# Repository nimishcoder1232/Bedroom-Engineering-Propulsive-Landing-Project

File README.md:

# Bedroom-Engineering-Propulsive-Landing-Project
This repo has everything that I made for my rocket that can propulsive landing, while still being under ITAR restrictions. 

For this project, I will design a rocket that can launch and then do a propulsive landing. In order to meet this challenge, I will have to make a new custom ESP32-based flight computer. I will have to make a quaternion orientation calculation system, I will have to design a control loop, and I will have to make a simulator in Python, without vibe coding, because it is too complicated. The simulator will simulate the rocket’s flight to help tune the control loop and the propulsive landing.

I did this project for a few reasons. The first reason I did it, is because in gneral, this is my passion. I love both engineering and rockets, so this is satisfactory for me. This isant a project for me, this project is more, who I am. I also made this project to learn from it. Throughout this project, I have learned sooo much, PCB design, CAD, Programign in many languages, soldering. And SO much more. Every time I sit down to do one of these projects, I end up learning so much. That is the second reason I work on these projects, To learn From them. 

Notes:
I am 3d printing everything myself, I DONT need reinbursment

The cad has all the parts. The engine, and the dc motor, and the syringes, are provided by me. 

The cad is ONE zip file. Once you unpack it, it has ALL the parts. the file in ALL CAPS called FULL ASEMBLY is the completed asembbly. 

No explosives are in any of the BOM, no engines, nothing. 

Project Link: https://blueprint.hackclub.com/projects/7459

Full Rocket: 

PCB schematic: 

PCB Routing: 

PCB Preview: 

Wiring Diagram: 

Any bold line is a electrical wire. I have color coded it. black for ground, red for power, and blue for saignals. if two same color lines touch, thats a connection, if two ddifferent colored lines overlaped, thats NOT a connection. 

|Item Name                                                              |Link                                                                                                                                                                                                                                                              |Quanity|Cost  USD|Notes                                                                             |
|-----------------------------------------------------------------------|------------------------------------------------------------------------------------------------------------------------------------------------------------------------------------------------------------------------------------------------------------------|-------|---------|----------------------------------------------------------------------------------|
|Carbon Fiber Rod 500mm 5 pack                                          |https://www.aliexpress.com/item/3256806607506929.html?spm=a2g0o.cart.0.0.1c3e38dawG7N6Z&mp=1&pdp_npi=6%40dis%21USD%21USD%209.39%21USD%208.29%21%21USD%208.29%21%21%21%402103110517673286269392021e3c62%2112000038324054750%21ct%21US%216511760370%21%212%210%21   |2      |9        |                                                                                  |
|drv8833 motor controler 1 pack                                         |https://www.aliexpress.com/item/3256809542138701.html?spm=a2g0o.cart.0.0.1c3e38dawG7N6Z&mp=1&pdp_npi=6%40dis%21USD%21USD%204.93%21USD%200.99%21%21USD%200.99%21%21%21%402103110517673286269392021e3c62%2112000049971286188%21ct%21US%216511760370%21%211%210%21   |1      |5        |                                                                                  |
|ES08MA &#124;&#124; servos 2 poack                                               |https://www.aliexpress.com/item/3256809559338882.html?spm=a2g0o.cart.0.0.1c3e38dawG7N6Z&mp=1&pdp_npi=6%40dis%21USD%21USD%2031.54%21USD%2013.51%21%21USD%2013.51%21%21%21%402103110517673286269392021e3c62%2112000050026083856%21ct%21US%216511760370%21%211%210%21|1      |15       |                                                                                  |
|Solder Paste                                                           |https://www.aliexpress.com/item/3256804805080766.html?spm=a2g0o.cart.0.0.1c3e38dawG7N6Z&mp=1&pdp_npi=6%40dis%21USD%21USD%207.42%21USD%207.11%21%21USD%207.11%21%21%21%402103110517673286269392021e3c62%2112000031264357461%21ct%21US%216511760370%21%211%210%21   |1      |7.11     |                                                                                  |
|Taxes deducted from Ali Express                                        |N.A.                                                                                                                                                                                                                                                              |1      |4        |                                                                                  |
|                                                                       |                                                                                                                                                                                                                                                                  |       |         |                                                                                  |
|USB4105-GF-A                                                           |https://www.digikey.com/en/products/detail/gct/USB4105-GF-A/11198441                                                                                                                                                                                              |2      |1.56     |Some of these components, I ordered extra because its LITTERLY cheaper to buy more|
|CP2102N-A02-GQFN28R                                                    |https://www.digikey.com/en/products/detail/silicon-labs/CP2102N-A02-GQFN28R/9863480                                                                                                                                                                               |2      |8.64     |                                                                                  |
|BMI270                                                                 |https://www.digikey.com/en/products/detail/bosch-sensortec/BMI270/9974486                                                                                                                                                                                         |2      |7.46     |                                                                                  |
|BMP390                                                                 |https://www.digikey.com/en/products/detail/bosch-sensortec/BMP390/16164575                                                                                                                                                                                        |2      |6.3      |                                                                                  |
|MMBT4401_R1_00001                                                      |https://www.digikey.com/en/products/detail/panjit-international-inc/MMBT4401-R1-00001/14661149                                                                                                                                                                    |4      |0.64     |                                                                                  |
|OSTTE020104                                                            |https://www.digikey.com/en/products/detail/on-shore-technology-inc/OSTTE020104/2351816                                                                                                                                                                            |10     |3.61     |                                                                                  |
|PS1240P02BT                                                            |https://www.digikey.com/en/products/detail/tdk-corporation/PS1240P02BT/935924                                                                                                                                                                                     |2      |1.24     |                                                                                  |
|CL21B106KOQNNNE                                                        |https://www.digikey.com/en/products/detail/samsung-electro-mechanics/CL21B106KOQNNNE/3888530                                                                                                                                                                      |15     |0.53     |                                                                                  |
|C0805C104K5RACTU                                                       |https://www.digikey.com/en/products/detail/kemet/C0805C104K5RACTU/411169                                                                                                                                                                                          |20     |0.32     |                                                                                  |
|B320A-13-F                                                             |https://www.digikey.com/en/products/detail/diodes-incorporated/B320A-13-F/717692                                                                                                                                                                                  |6      |1.56     |                                                                                  |
|ESD5Z5.0T5G                                                            |https://www.digikey.com/en/products/detail/onsemi/ESD5Z5-0T5G/5404303                                                                                                                                                                                             |10     |0.99     |                                                                                  |
|TPS565208DDCR                                                          |https://www.digikey.com/en/products/detail/texas-instruments/TPS565208DDCR/7776393                                                                                                                                                                                |2      |2.76     |                                                                                  |
|LD1117S33TR                                                            |https://www.digikey.com/en/products/detail/stmicroelectronics/LD1117S33TR/585766                                                                                                                                                                                  |2      |0.68     |                                                                                  |
|ESP32-S3-WROOM-1-N8                                                    |https://www.digikey.com/en/products/detail/espressif-systems/ESP32-S3-WROOM-1-N8/15200089                                                                                                                                                                         |2      |10.98    |                                                                                  |
|CL21B105KBFNNNE                                                        |https://www.digikey.com/en/products/detail/samsung-electro-mechanics/CL21B105KBFNNNE/3886687                                                                                                                                                                      |10     |0.13     |                                                                                  |
|CL21A226MAYNNNE                                                        |https://www.digikey.com/en/products/detail/samsung-electro-mechanics/CL21A226MAYNNNE/10479857                                                                                                                                                                     |3      |0.24     |                                                                                  |
|LTST-C170GKT                                                           |https://www.digikey.com/en/products/detail/liteon/LTST-C170GKT/269226                                                                                                                                                                                             |3      |0.3      |                                                                                  |
|AO3400A                                                                |https://www.digikey.com/en/products/detail/alpha-omega-semiconductor-inc/AO3400A/1855772                                                                                                                                                                          |10     |2.82     |                                                                                  |
|MLZ2012P220WT000                                                       |https://www.digikey.com/en/products/detail/tdk-corporation/MLZ2012P220WT000/4327893                                                                                                                                                                               |2      |0.2      |                                                                                  |
|CRCW08051K00FKEA                                                       |https://www.digikey.com/en/products/detail/vishay-dale/CRCW08051K00FKEA/1175637                                                                                                                                                                                   |2      |0.2      |                                                                                  |
|RMCF0805FT22K1                                                         |https://www.digikey.com/en/products/detail/stackpole-electronics-inc/RMCF0805FT22K1/1760211                                                                                                                                                                       |10     |0.07     |                                                                                  |
|RMCF0805FT10K0                                                         |https://www.digikey.com/en/products/detail/stackpole-electronics-inc/RMCF0805FT10K0/1760676                                                                                                                                                                       |16     |0.21     |                                                                                  |
|RC0805JR-075K1L                                                        |https://www.digikey.com/en/products/detail/yageo/RC0805JR-075K1L/728338                                                                                                                                                                                           |10     |0.08     |                                                                                  |
|W25Q128JVSIM                                                           |https://www.digikey.com/en/products/detail/winbond-electronics/W25Q128JVSIM/6819721                                                                                                                                                                               |2      |3.94     |                                                                                  |
|RC0805FR-072K2L                                                        |https://www.digikey.com/en/products/detail/yageo/RC0805FR-072K2L/727676                                                                                                                                                                                           |10     |0.1      |                                                                                  |
|RC0805FR-0747K5L                                                       |https://www.digikey.com/en/products/detail/yageo/RC0805FR-0747K5L/727975                                                                                                                                                                                          |10     |0.1      |                                                                                  |
|RT0805BRD0759R7L                                                       |https://www.digikey.com/en/products/detail/yageo/RT0805BRD0759R7L/7708567                                                                                                                                                                                         |2      |0.32     |                                                                                  |
|RC0805FR-07330RL                                                       |https://www.digikey.com/en/products/detail/yageo/RC0805FR-07330RL/727866                                                                                                                                                                                          |10     |0.1      |                                                                                  |
|Dijikey Shipping                                                       |N.A.                                                                                                                                                                                                                                                              |1      |7        |                                                                                  |
|Sales tax + terrifs (Dijikey)                                          |N.A.                                                                                                                                                                                                                                                              |1      |8        |                                                                                  |
|                                                                       |                                                                                                                                                                                                                                                                  |       |         |                                                                                  |
|JLCPCB 4 Layer PCB + stencil + Global Standard Dirrect Line + sales tax|JLC PCB                                                                                                                                                                                                                                                           |5      |33       |                                                                                  |
|                                                                       |                                                                                                                                                                                                                                                                  |       |         |                                                                                  |
|JLC PCB order                                                          |33                                                                                                                                                                                                                                                                |       |         |                                                                                  |
|                                                                       |                                                                                                                                                                                                                                                                  |       |         |                                                                                  |
|Ali express order                                                      |40.11                                                                                                                                                                                                                                                             |       |         |                                                                                  |
|                                                                       |                                                                                                                                                                                                                                                                  |       |         |                                                                                  |
|Dijikey Order                                                          |71.08                                                                                                                                                                                                                                                             |       |         |                                                                                  |
|                                                                       |                                                                                                                                                                                                                                                                  |       |         |                                                                                  |
|Total Cost                                                             |144.19                                                                                                                                                                                                                                                            |       |         |                                                                                  |

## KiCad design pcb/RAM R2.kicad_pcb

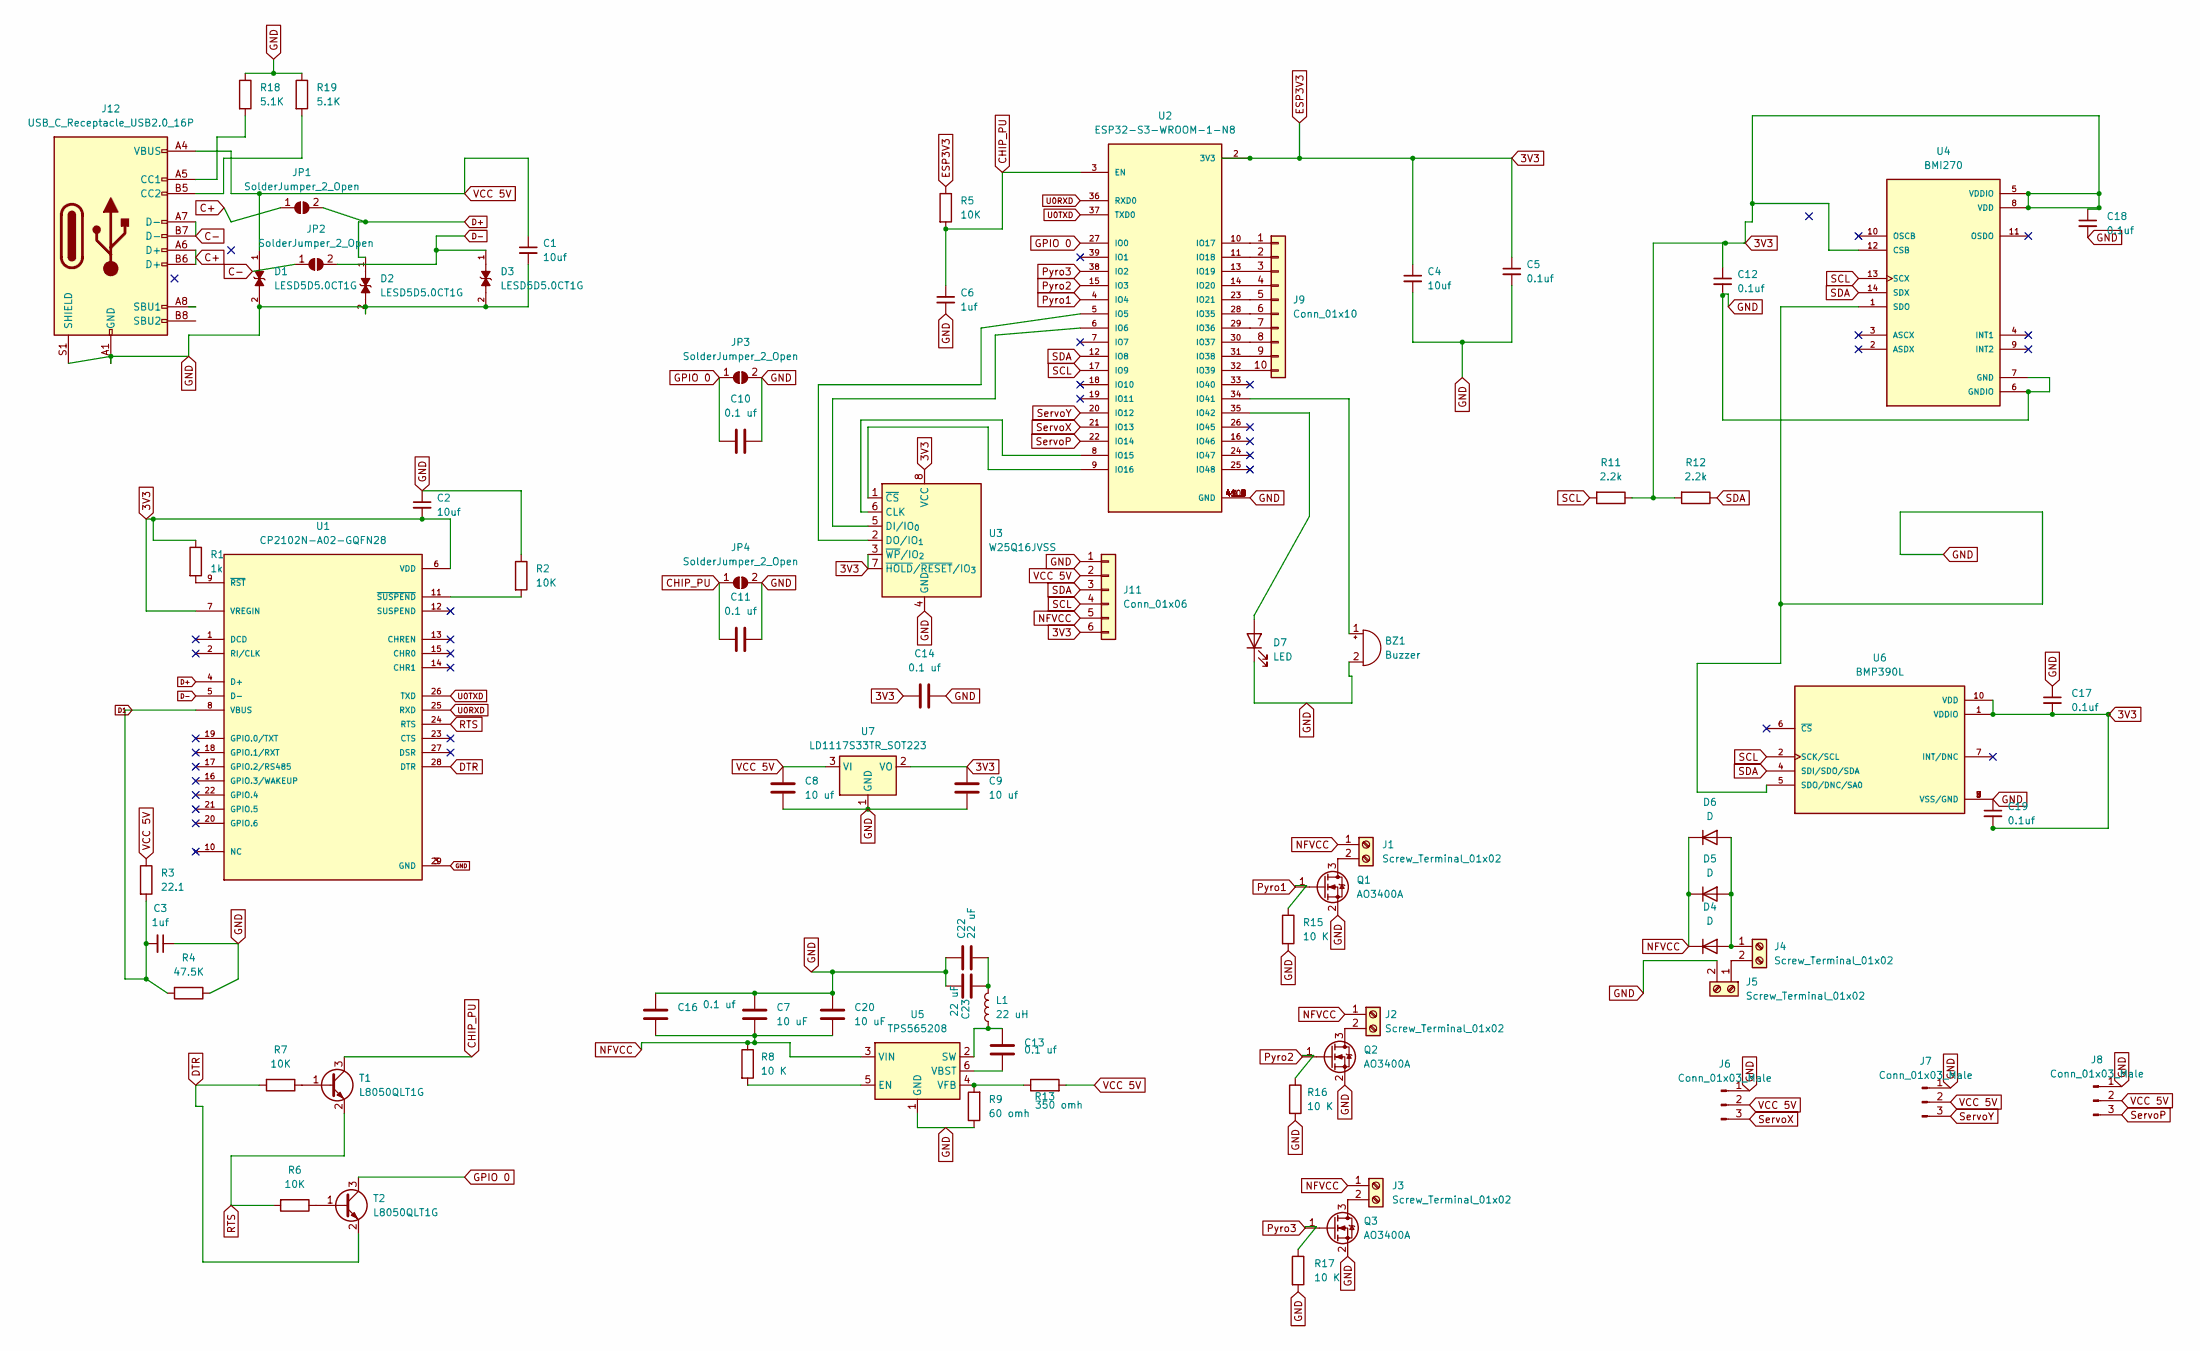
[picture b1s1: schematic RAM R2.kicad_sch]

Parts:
BZ1: Buzzer; Buzzer_TDK_PS1240P02BT_D12.2mm_H6.5mm
C1, C2, C4: 10uf; C_0805_2012Metric
C3, C6: 1uf; C_0805_2012Metric
C5, C12, C17, C18, C19: 0.1uf; C_0805_2012Metric
C7, C20: 10 uF; C_0805_2012Metric
C8, C9: 10 uf; C_0805_2012Metric
C10, C11, C13, C14, C16: 0.1 uf; C_0805_2012Metric
C22, C23: 22 uF; C_0805_2012Metric
D1, D2, D3: LESD5D5.0CT1G; TVS_LESD5D5.0CT1G; PARTREV O
D4, D5, D6: D; D_SMA
D7: LED; LED_0805_2012Metric
J1, J2, J3, J4, J5: Screw_Terminal_01x02; TerminalBlock_4Ucon_1x02_P3.50mm_Horizontal
J6, J7, J8: Conn_01x03_Male; PinHeader_1x03_P2.54mm_Vertical
J9: Conn_01x10; 10 pad genaric
J11: Conn_01x06; 6pad genaric
J12: USB_C_Receptacle_USB2.0_16P; USB_C_Receptacle_GCT_USB4105-xx-A_16P_TopMnt_Horizontal
JP1, JP2, JP3, JP4: SolderJumper_2_Open; SolderJumper-2_P1.3mm_Open_Pad1.0x1.5mm
L1: 22 uH; L_0805_2012Metric
Q1, Q2, Q3: AO3400A; SOT-23
R1: 1k; R_0805_2012Metric
R2, R5, R6, R7: 10K; R_0805_2012Metric
R3: 22.1; R_0805_2012Metric
R4: 47.5K; R_0805_2012Metric
R8, R15, R16, R17: 10 K; R_0805_2012Metric
R9: 60 omh; R_0805_2012Metric
R11, R12: 2.2k; R_0805_2012Metric
R13: 350 omh; R_0805_2012Metric
R18, R19: 5.1K; R_0805_2012Metric
T1, T2: L8050QLT1G; SOT-23
U1: CP2102N-A02-GQFN28; QFN50P500X500X80-29N; PARTREV 1.5
U2: ESP32-S3-WROOM-1-N8; XCVR_ESP32-S3-WROOM-1-N8
U3: W25Q16JVSS; SOIC-8_5.3x5.3mm_P1.27mm
U4: BMI270; XDCR_BMI270
U5: TPS565208; SOT-23-6
U6: BMP390L; XDCR_BMP390L; PARTREV 1.7
U7: LD1117S33TR_SOT223; SOT-223-3_TabPin2

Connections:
3V3: C2.2, C4.1, C5.1, C9.1, C12.1, C14.2, C17.2, C18.1, C19.2, J11.6, R1.1, R5.1, R11.1, R12.2, U1.6 (VDD), U1.7 (VREGIN), U2.2 (3V3), U3.3 (~WP/IO_{2}), U3.7 (~HOLD/~RESET/IO_{3}), U3.8 (VCC), U4.5 (VDDIO), U4.8 (VDD), U4.12 (CSB), U6.1 (VDDIO), U6.10 (VDD), U7.2 (VO)
C+: J12.A6 (D+), J12.B6 (D+), JP1.1 (A)
C-: J12.A7 (D-), J12.B7 (D-), JP2.1 (A)
CHIP_PU: C6.1, C11.2, JP4.1 (A), R5.2, T1.3 (C), U2.3 (EN)
D1: C3.2, R3.2, R4.2, U1.8 (VBUS)
D+: D2.1, JP1.2 (B), U1.4 (D+)
D-: D3.1, JP2.2 (B), U1.5 (D-)
DTR: R7.2, T2.2 (E), U1.28 (DTR)
GND: BZ1.2 (+), C1.2, C2.1, C3.1, C4.2, C5.2, C6.2, C7.1, C8.2, C9.2, C10.1, C11.1, C12.2, C14.1, C16.1, C17.1, C18.2, C19.1, C20.1, C22.1, C23.1, D1.2, D2.2, D3.2, D7.1 (K), J5.2, J6.1, J7.1, J8.1, J11.1, J12.A1 (GND), J12.A12 (GND), J12.B1 (GND), J12.B12 (GND), J12.S1 (SHIELD), JP3.2 (B), JP4.2 (B), Q1.2 (S), Q2.2 (S), Q3.2 (S), R2.1, R4.1, R9.1, R15.2, R16.2, R17.2, R18.1, R19.1, U1.3 (GND), U1.29 (GND), U2.1 (GND), U2.40 (GND), U2.41_1 (GND), U2.41_2 (GND), U2.41_3 (GND), U2.41_4 (GND), U2.41_5 (GND), U2.41_6 (GND), U2.41_7 (GND), U2.41_8 (GND), U2.41_9 (GND), U3.4 (GND), U4.1 (SDO), U4.6 (GNDIO), U4.7 (GND), U5.1 (GND), U6.3 (VSS/GND), U6.5 (SDO/DNC/SA0), U6.8 (VSS/GND), U6.9 (VSS/GND), U7.1 (GND)
GPIO 0: C10.2, JP3.1 (A), T2.3 (C), U2.27 (IO0)
NFVCC: C7.2, C16.2, C20.2, D4.1 (K), D5.1 (K), D6.1 (K), J1.1, J2.1, J3.1, J11.5, R8.1, U5.3 (VIN)
unnamed: BZ1.1 (-), U2.34 (IO41)
unnamed: C22.2, C23.2, L1.2
unnamed: D4.2 (A), D5.2 (A), D6.2 (A), J4.1
unnamed: D7.2 (A), U2.35 (IO42)
unnamed: J1.2, Q1.3 (D)
unnamed: J2.2, Q2.3 (D)
unnamed: J3.2, Q3.3 (D)
unnamed: J4.2, J5.1
unnamed: J9.1, U2.10 (IO17)
unnamed: J9.2, U2.11 (IO18)
unnamed: J9.3, U2.13 (IO19)
unnamed: J9.4, U2.14 (IO20)
unnamed: J9.5, U2.23 (IO21)
unnamed: J9.6, U2.28 (IO35)
unnamed: J9.7, U2.29 (IO36)
unnamed: J9.8, U2.30 (IO37)
unnamed: J9.9, U2.31 (IO38)
unnamed: J9.10, U2.32 (IO39)
unnamed: J12.A5 (CC1), R18.2
unnamed: J12.B5 (CC2), R19.2
unnamed: R7.1, T1.1 (B)
unnamed: R6.1, T2.1 (B)
unnamed: R1.2, U1.9 (~RST)
unnamed: R2.2, U1.11 (~SUSPEND)
unnamed: U2.5 (IO5), U3.2 (DO/IO_{1})
unnamed: U2.6 (IO6), U3.5 (DI/IO_{0})
unnamed: U2.8 (IO15), U3.6 (CLK)
unnamed: U2.9 (IO16), U3.1 (~CS)
unnamed: R8.2, U5.5 (EN)
unnamed: C13.1, L1.1, U5.2 (SW)
unnamed: C13.2, U5.6 (VBST)
unnamed: R9.2, R13.1, U5.4 (VFB)
Pyro1: Q1.1 (G), R15.1, U2.4 (IO4)
Pyro2: Q2.1 (G), R16.1, U2.15 (IO3)
Pyro3: Q3.1 (G), R17.1, U2.38 (IO2)
RTS: R6.2, T1.2 (E), U1.24 (RTS)
SCL: J11.4, R11.2, U2.17 (IO9), U4.13 (SCX), U6.2 (SCK/SCL)
SDA: J11.3, R12.1, U2.12 (IO8), U4.14 (SDX), U6.4 (SDI/SDO/SDA)
ServoP: J8.3, U2.22 (IO14)
ServoX: J6.3, U2.21 (IO13)
ServoY: J7.3, U2.20 (IO12)
U0RXD: U1.25 (RXD), U2.36 (RXD0)
U0TXD: U1.26 (TXD), U2.37 (TXD0)
VCC 5V: C1.1, C8.1, D1.1, J6.2, J7.2, J8.2, J11.2, J12.A4 (VBUS), J12.A9 (VBUS), J12.B4 (VBUS), J12.B9 (VBUS), R3.1, R13.2, U7.3 (VI)

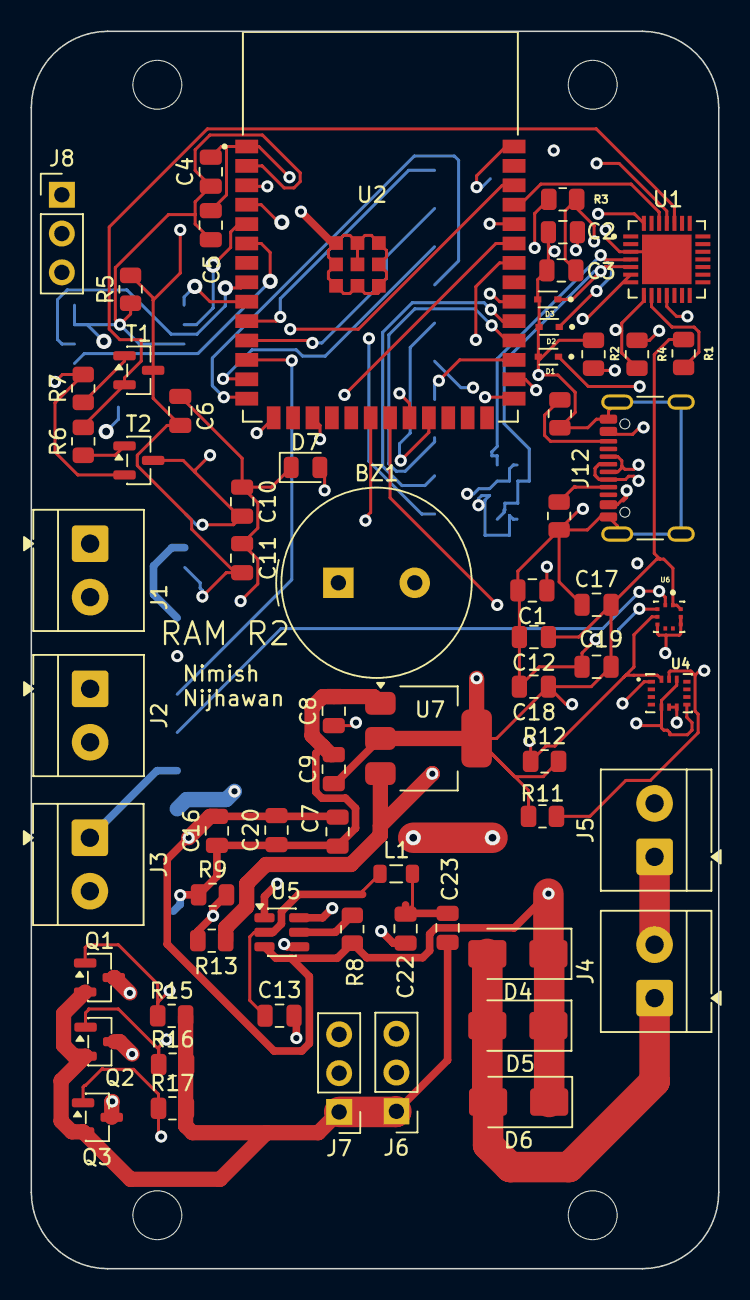
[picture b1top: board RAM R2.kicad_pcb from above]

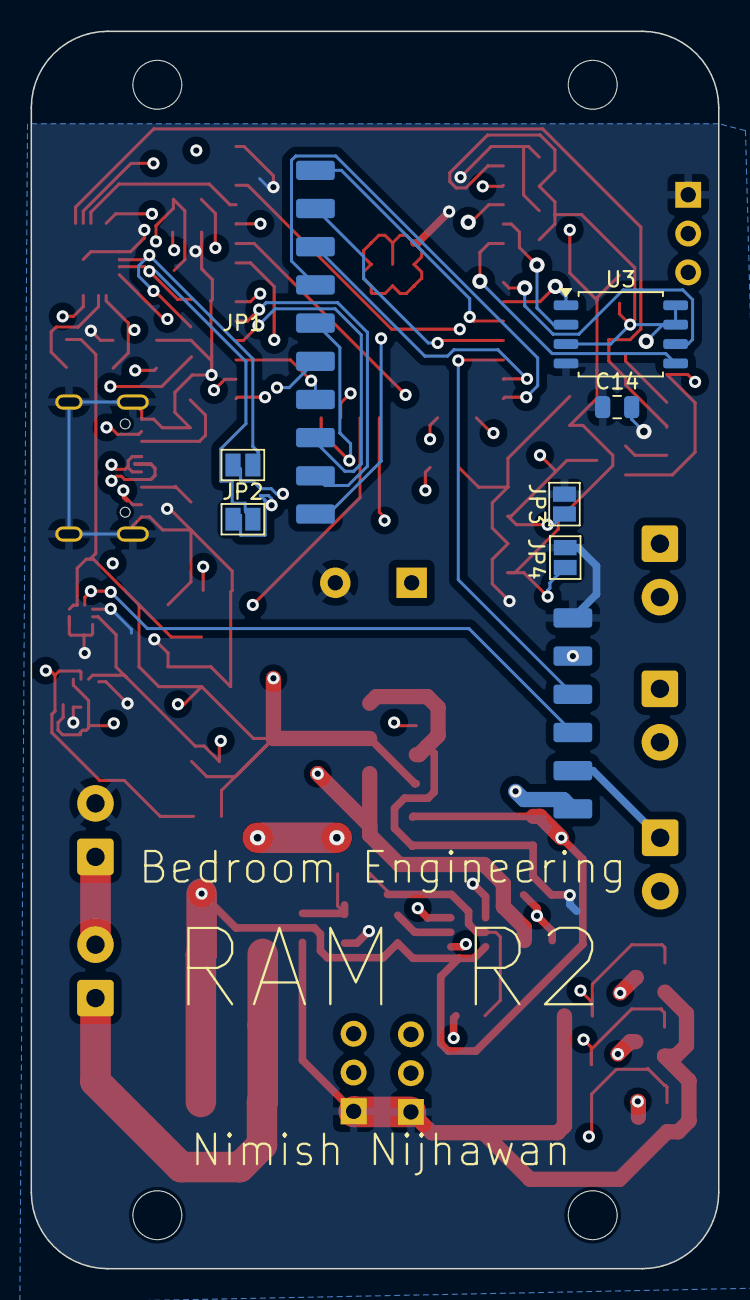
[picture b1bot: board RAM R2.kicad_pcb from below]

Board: 4 copper layers, 45.0 x 81.0 mm, 74 parts (8 on the bottom side), 55 nets.

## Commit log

2025-12-25 Initialize README with project details
    Added project title and description to README
2025-12-30 Enhance README with project details and images
    Expanded project description and added images.
2025-12-30 Rename RAM R2.kicad_pcb to pcb/RAM R2.kicad_pcb
2025-12-30 Rename RAM R2.kicad_prl to pcb/RAM R2.kicad_prl
2025-12-30 Rename RAM R2.kicad_pro to pcb/RAM R2.kicad_pro
2025-12-31 Rename RAM R2.kicad_sch to pcb/RAM R2.kicad_sch
2025-12-31 Rename RAMR2.zip to RAMR2Gerber.zip
2025-12-31 Add rocket flight simulation with PID tuning
    This program simulates a rocket's flight characteristics and allows tuning of PID variables. It includes physics constants and implements thrust calculations based on gimbal angles.
2025-12-31 Improve comments and fix spelling in flight computer test
    Updated comments for clarity and corrected spelling errors.
2025-12-31 Update README with project details and corrections
    Corrected typos and added notes about project resources.
2025-12-31 Rename full asembly.step to cad/full asembly.step
2025-12-31 Fix typos and clarify project notes in README
    Corrected typos and improved clarity in project description.
2025-12-31 Update README with component list and costs
    Added detailed itemized list of components with links, quantities, and costs to the README.
2026-01-05 Rename CAD.zip to cad/CAD.zip
2026-01-05 Fix typos and formatting in README.md
    Corrected spelling and formatting issues in README.
2026-01-05 Fix typo in BOM description in README.md
2026-01-05 Enhance README with wiring diagram and details
    Added wiring diagram and explanation to README.
2026-01-07 Fix typos and enhance README clarity
    Corrected typos and improved clarity in project description.
